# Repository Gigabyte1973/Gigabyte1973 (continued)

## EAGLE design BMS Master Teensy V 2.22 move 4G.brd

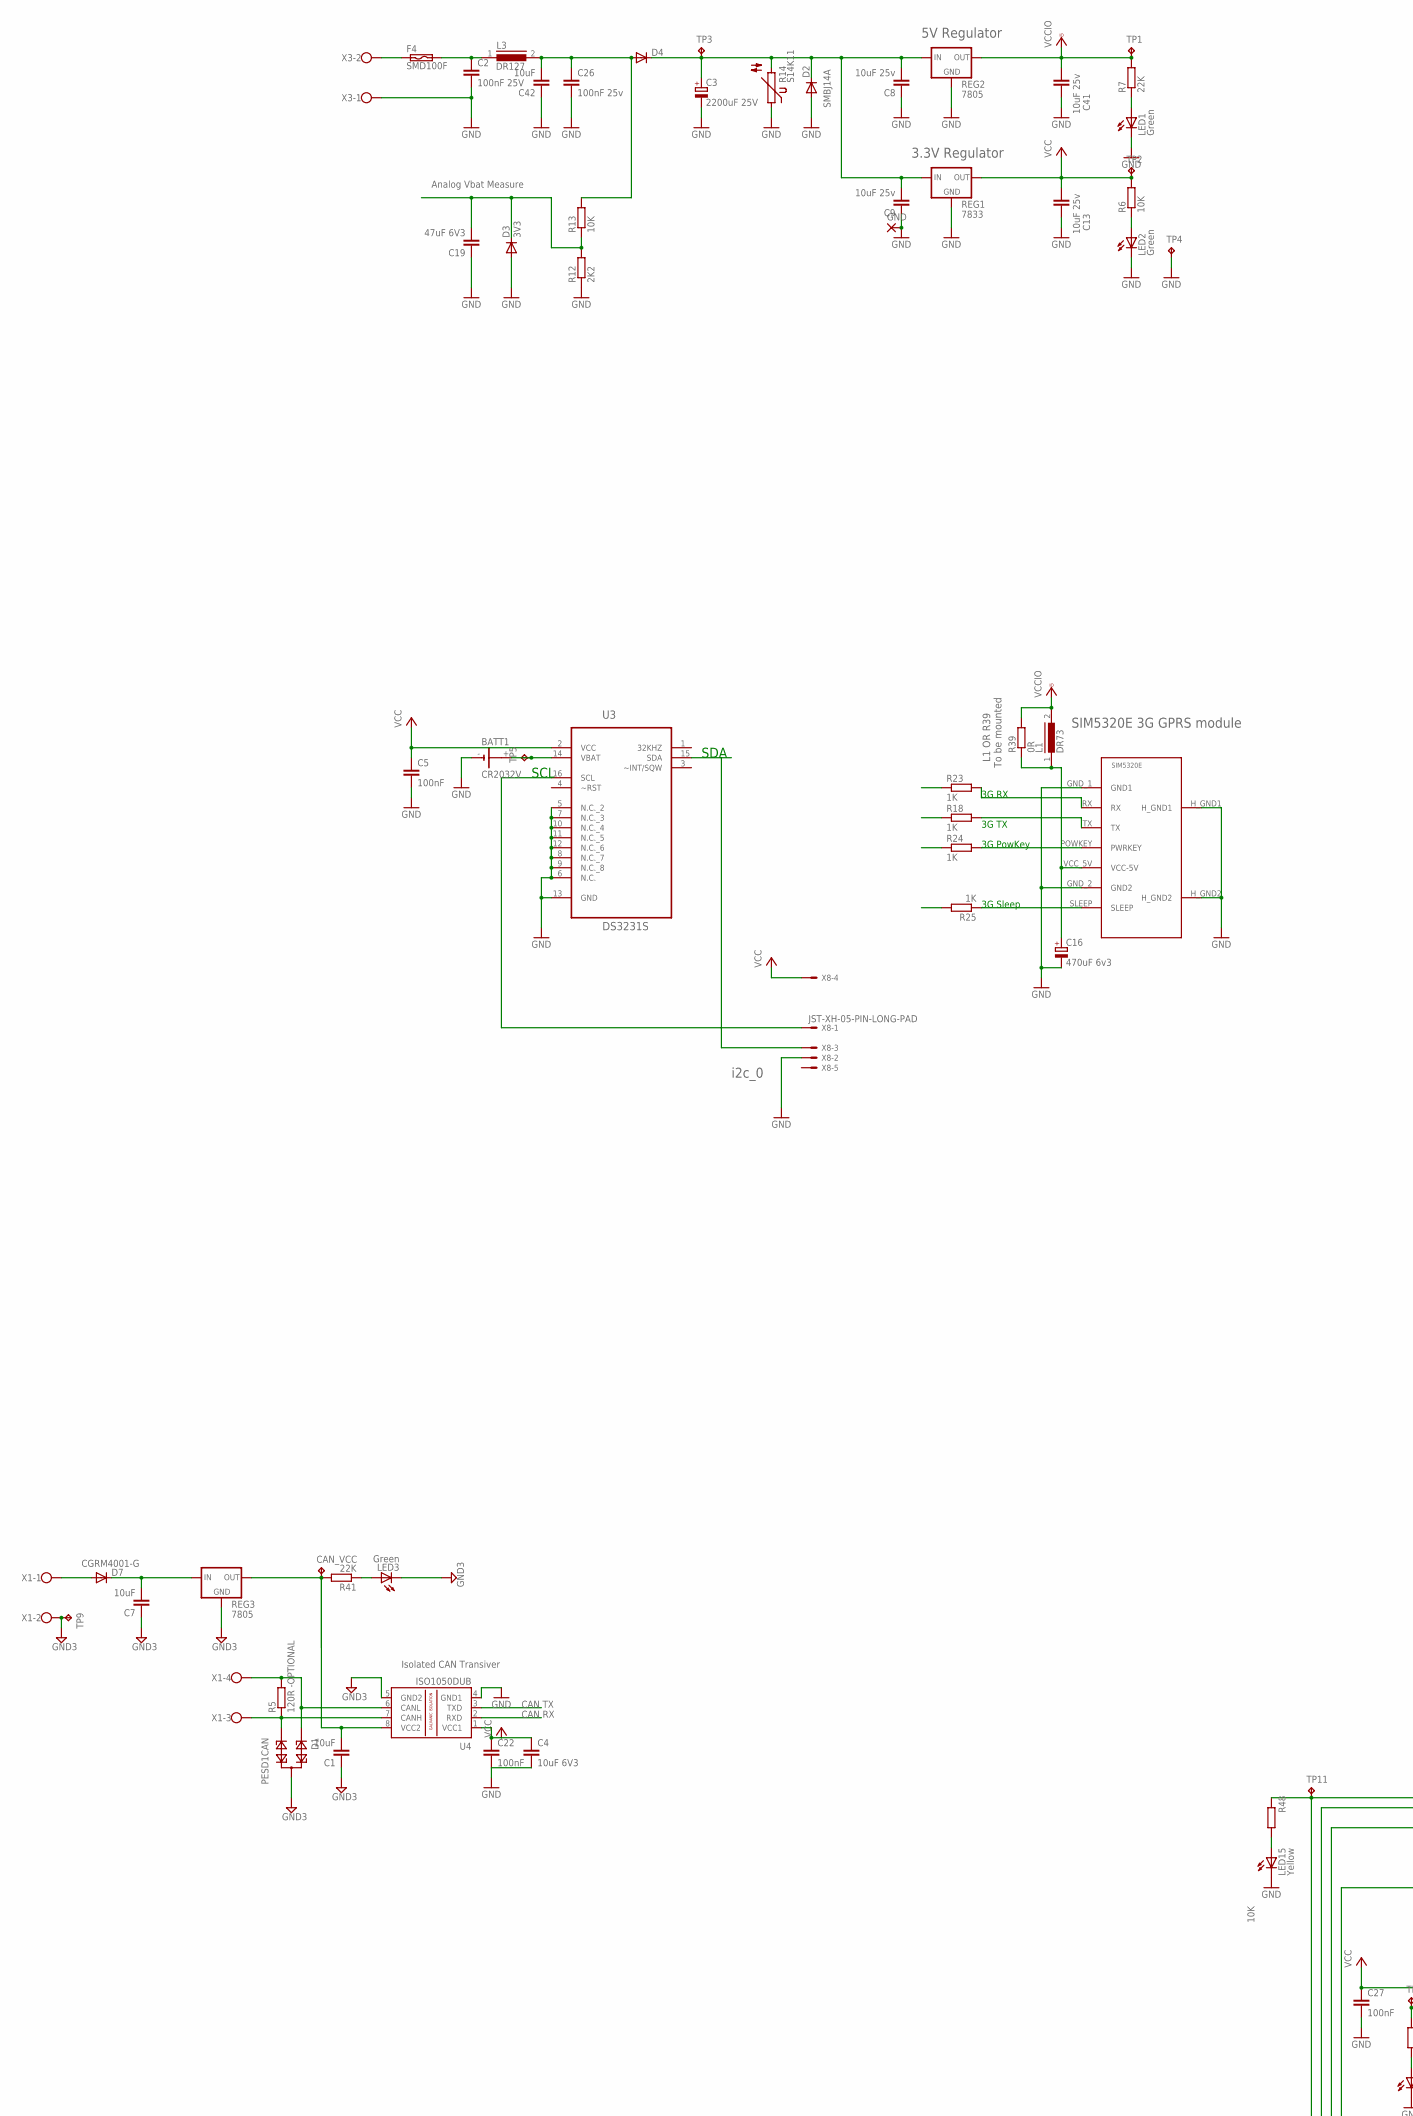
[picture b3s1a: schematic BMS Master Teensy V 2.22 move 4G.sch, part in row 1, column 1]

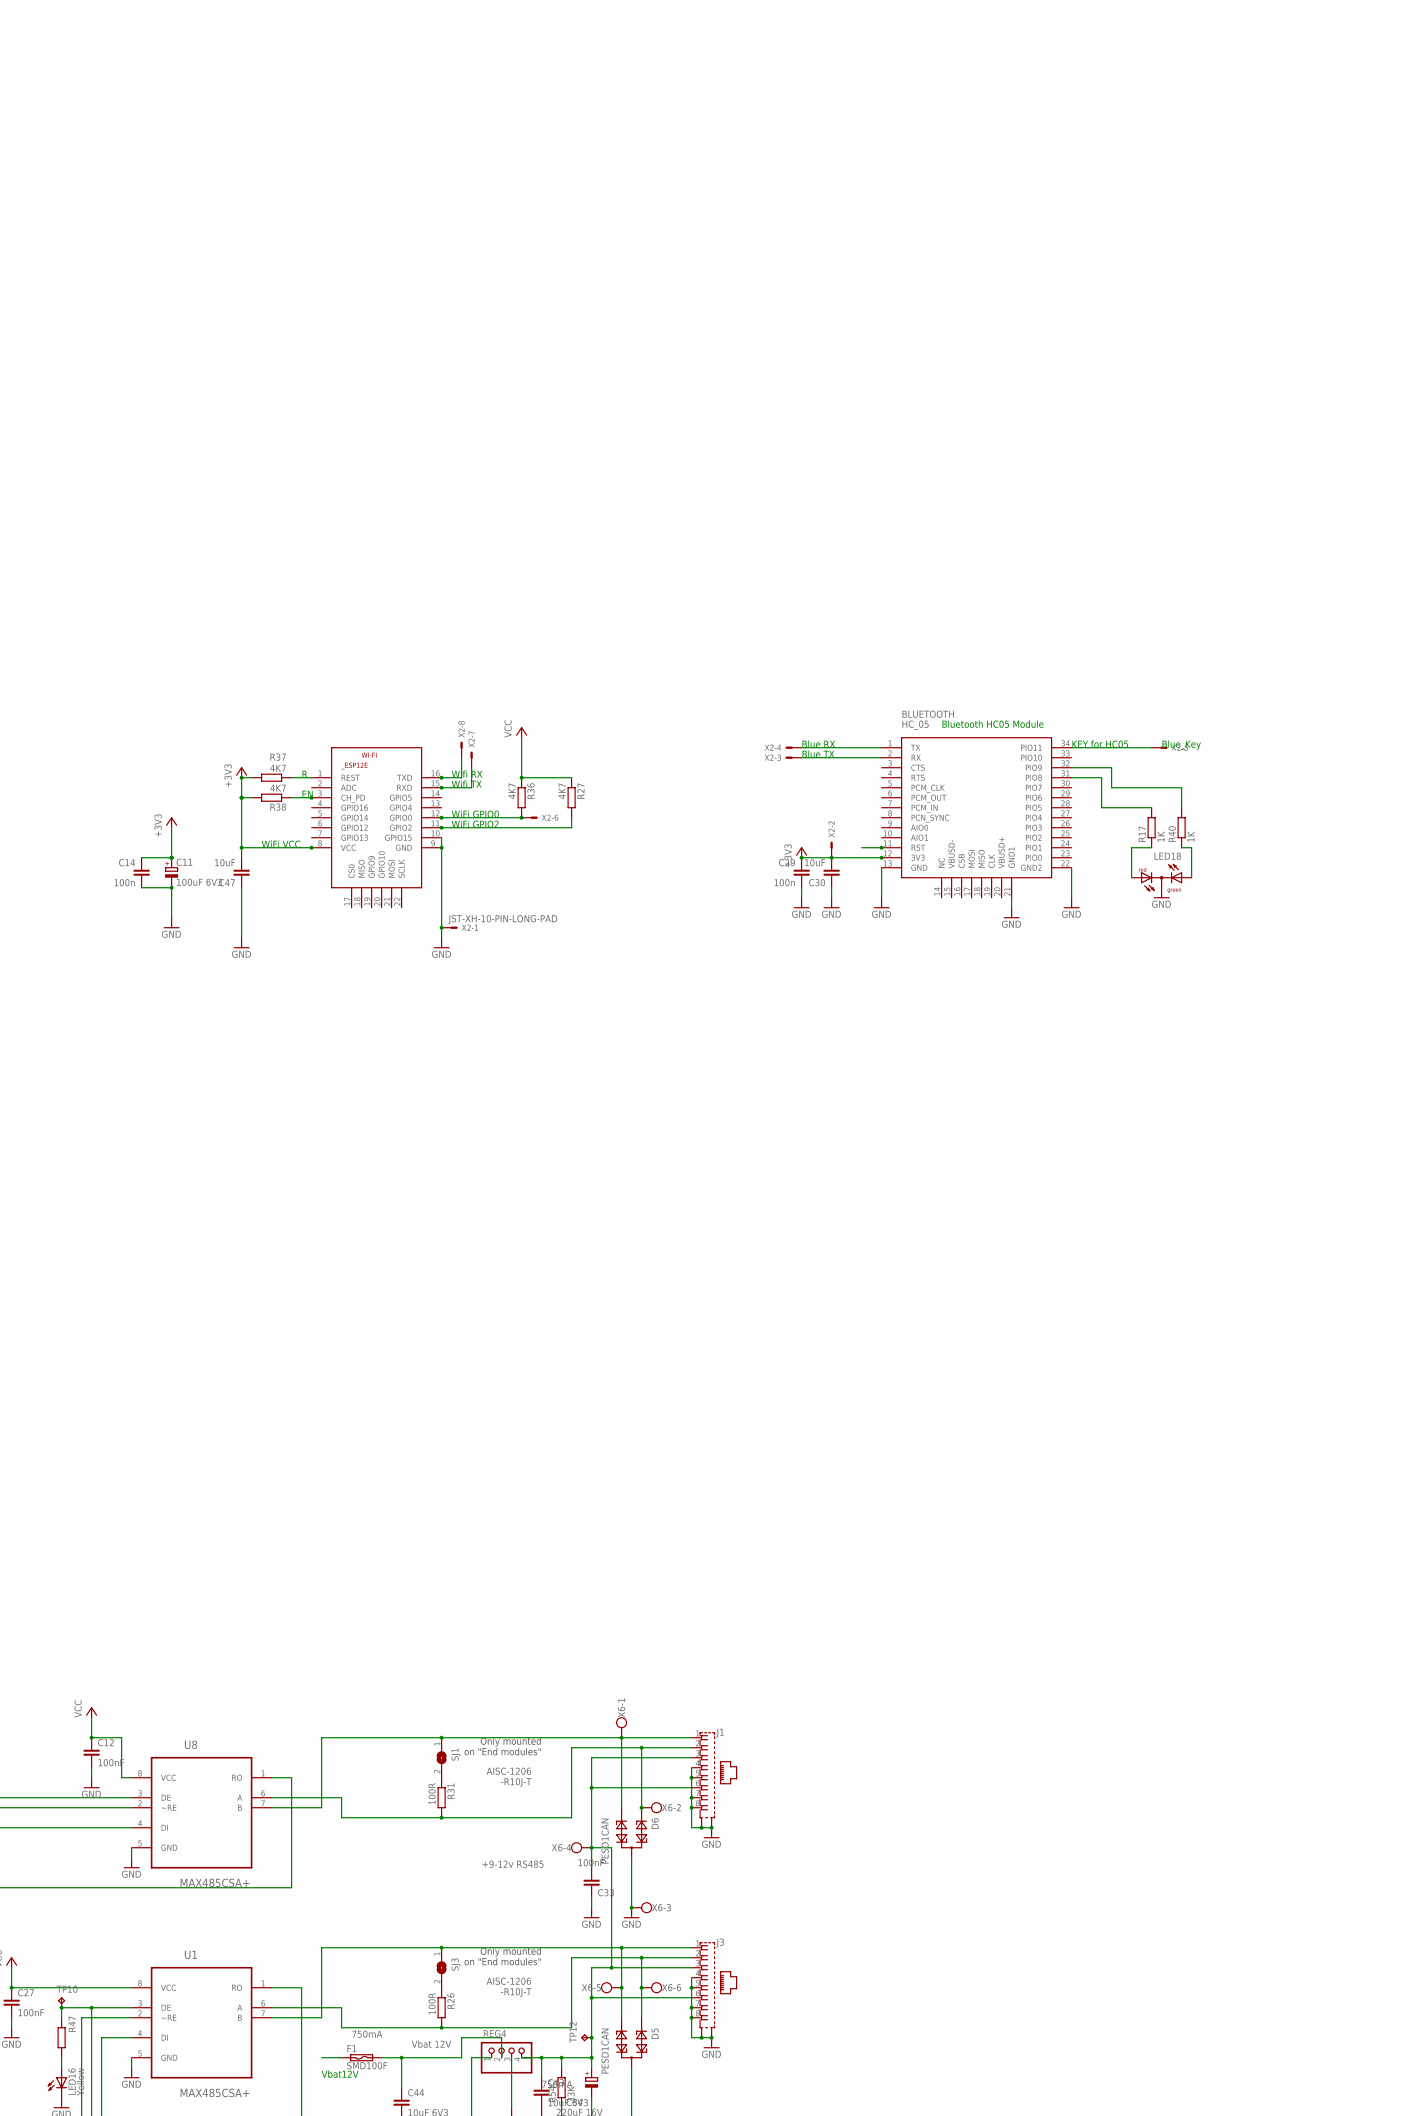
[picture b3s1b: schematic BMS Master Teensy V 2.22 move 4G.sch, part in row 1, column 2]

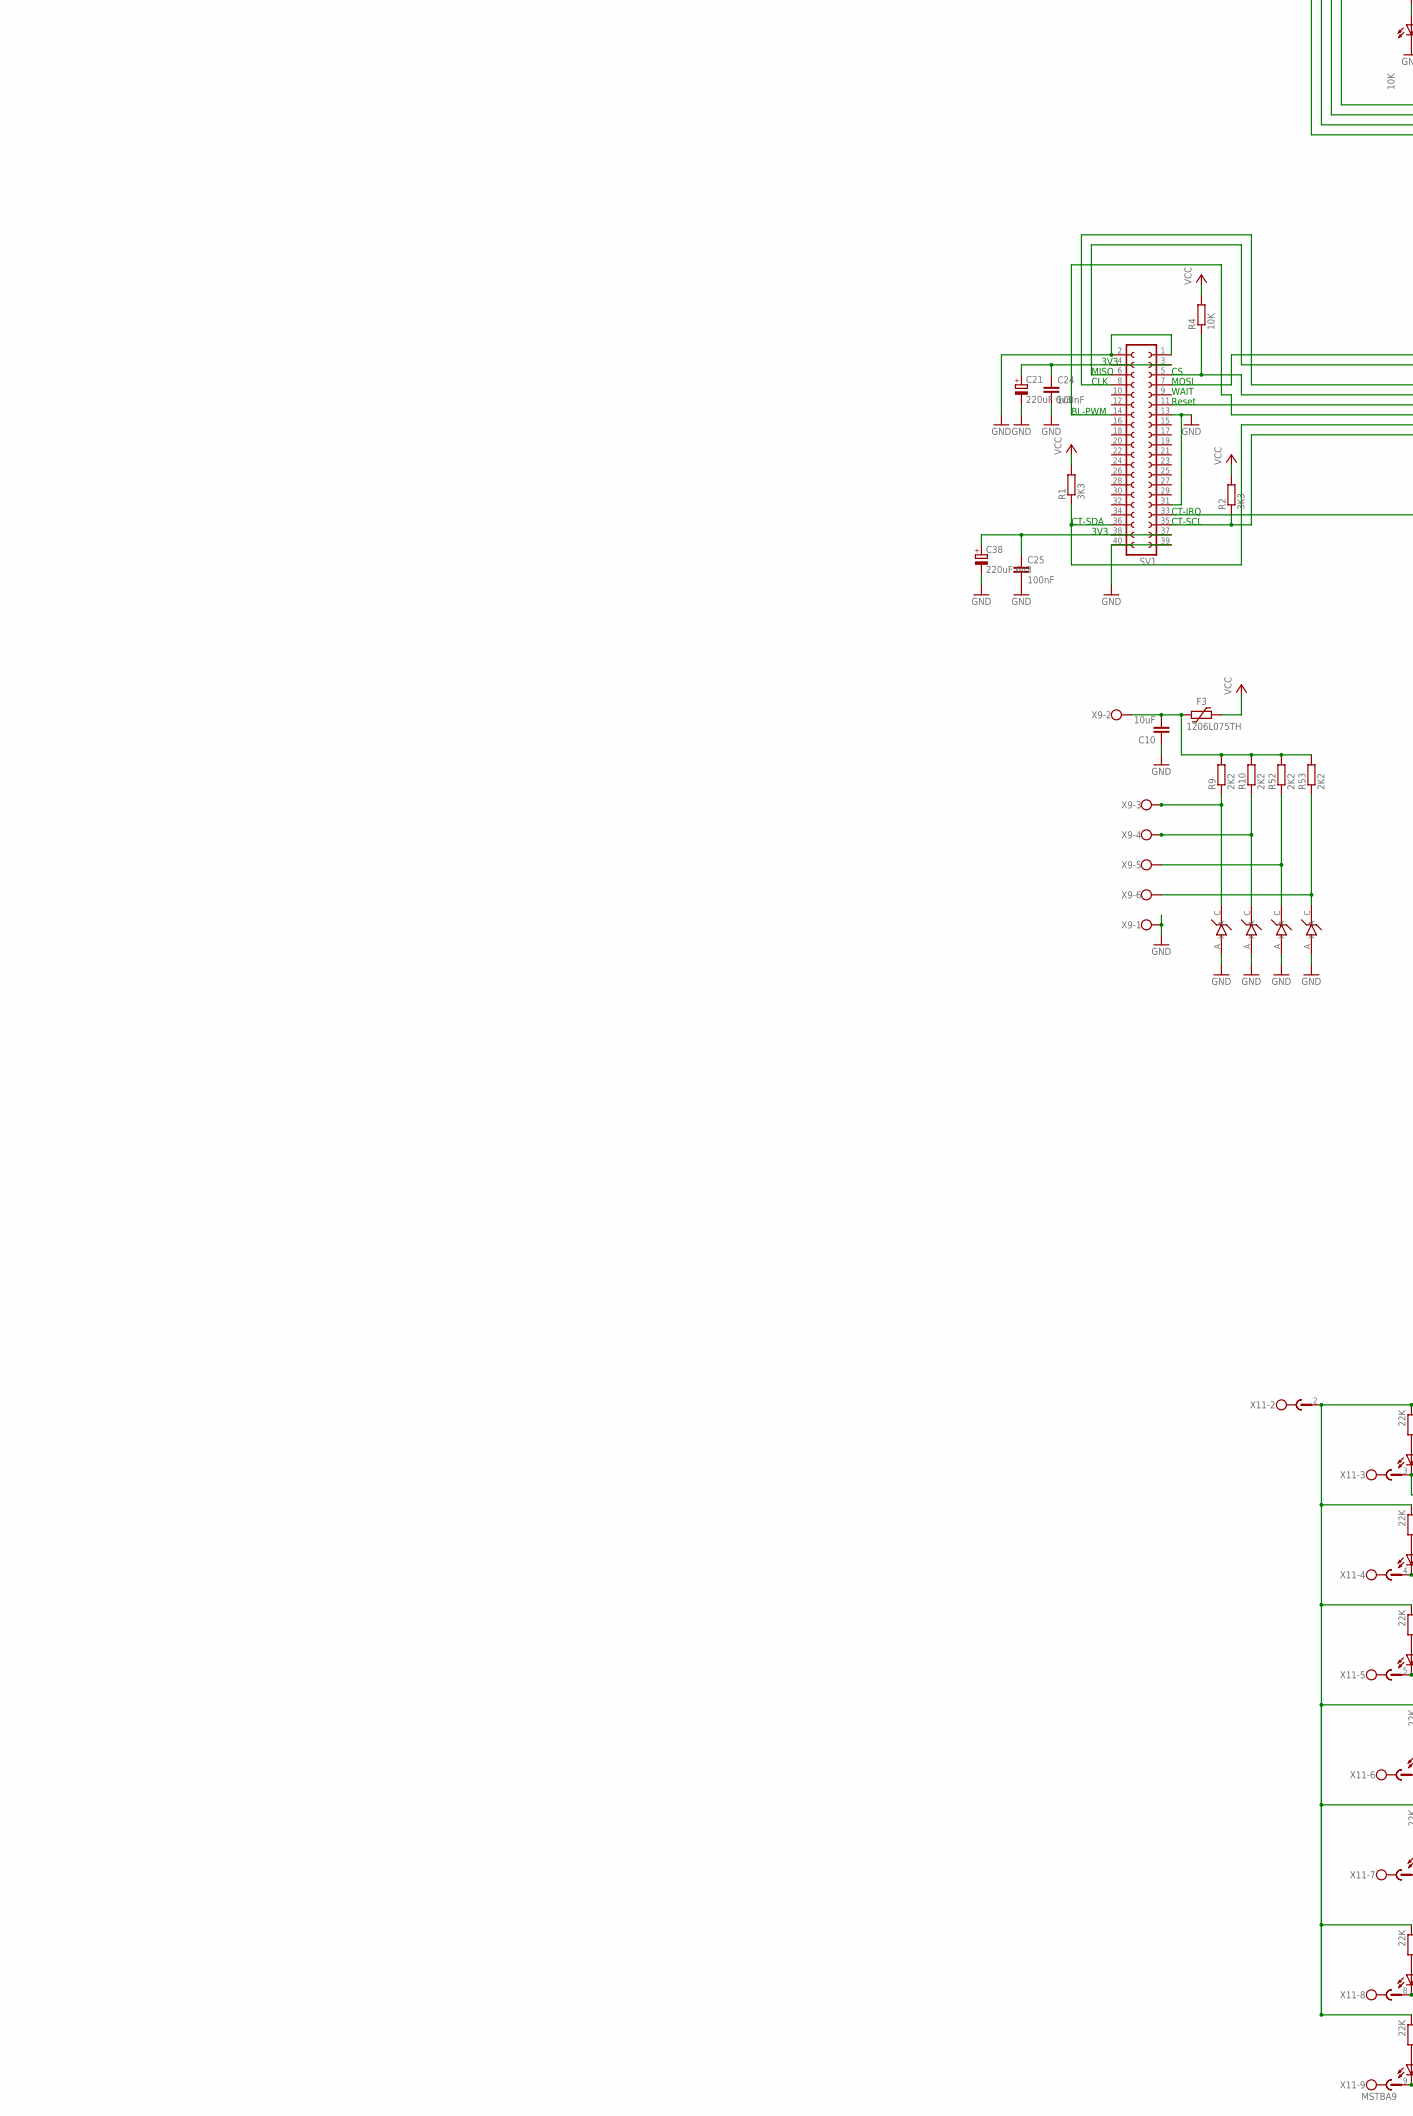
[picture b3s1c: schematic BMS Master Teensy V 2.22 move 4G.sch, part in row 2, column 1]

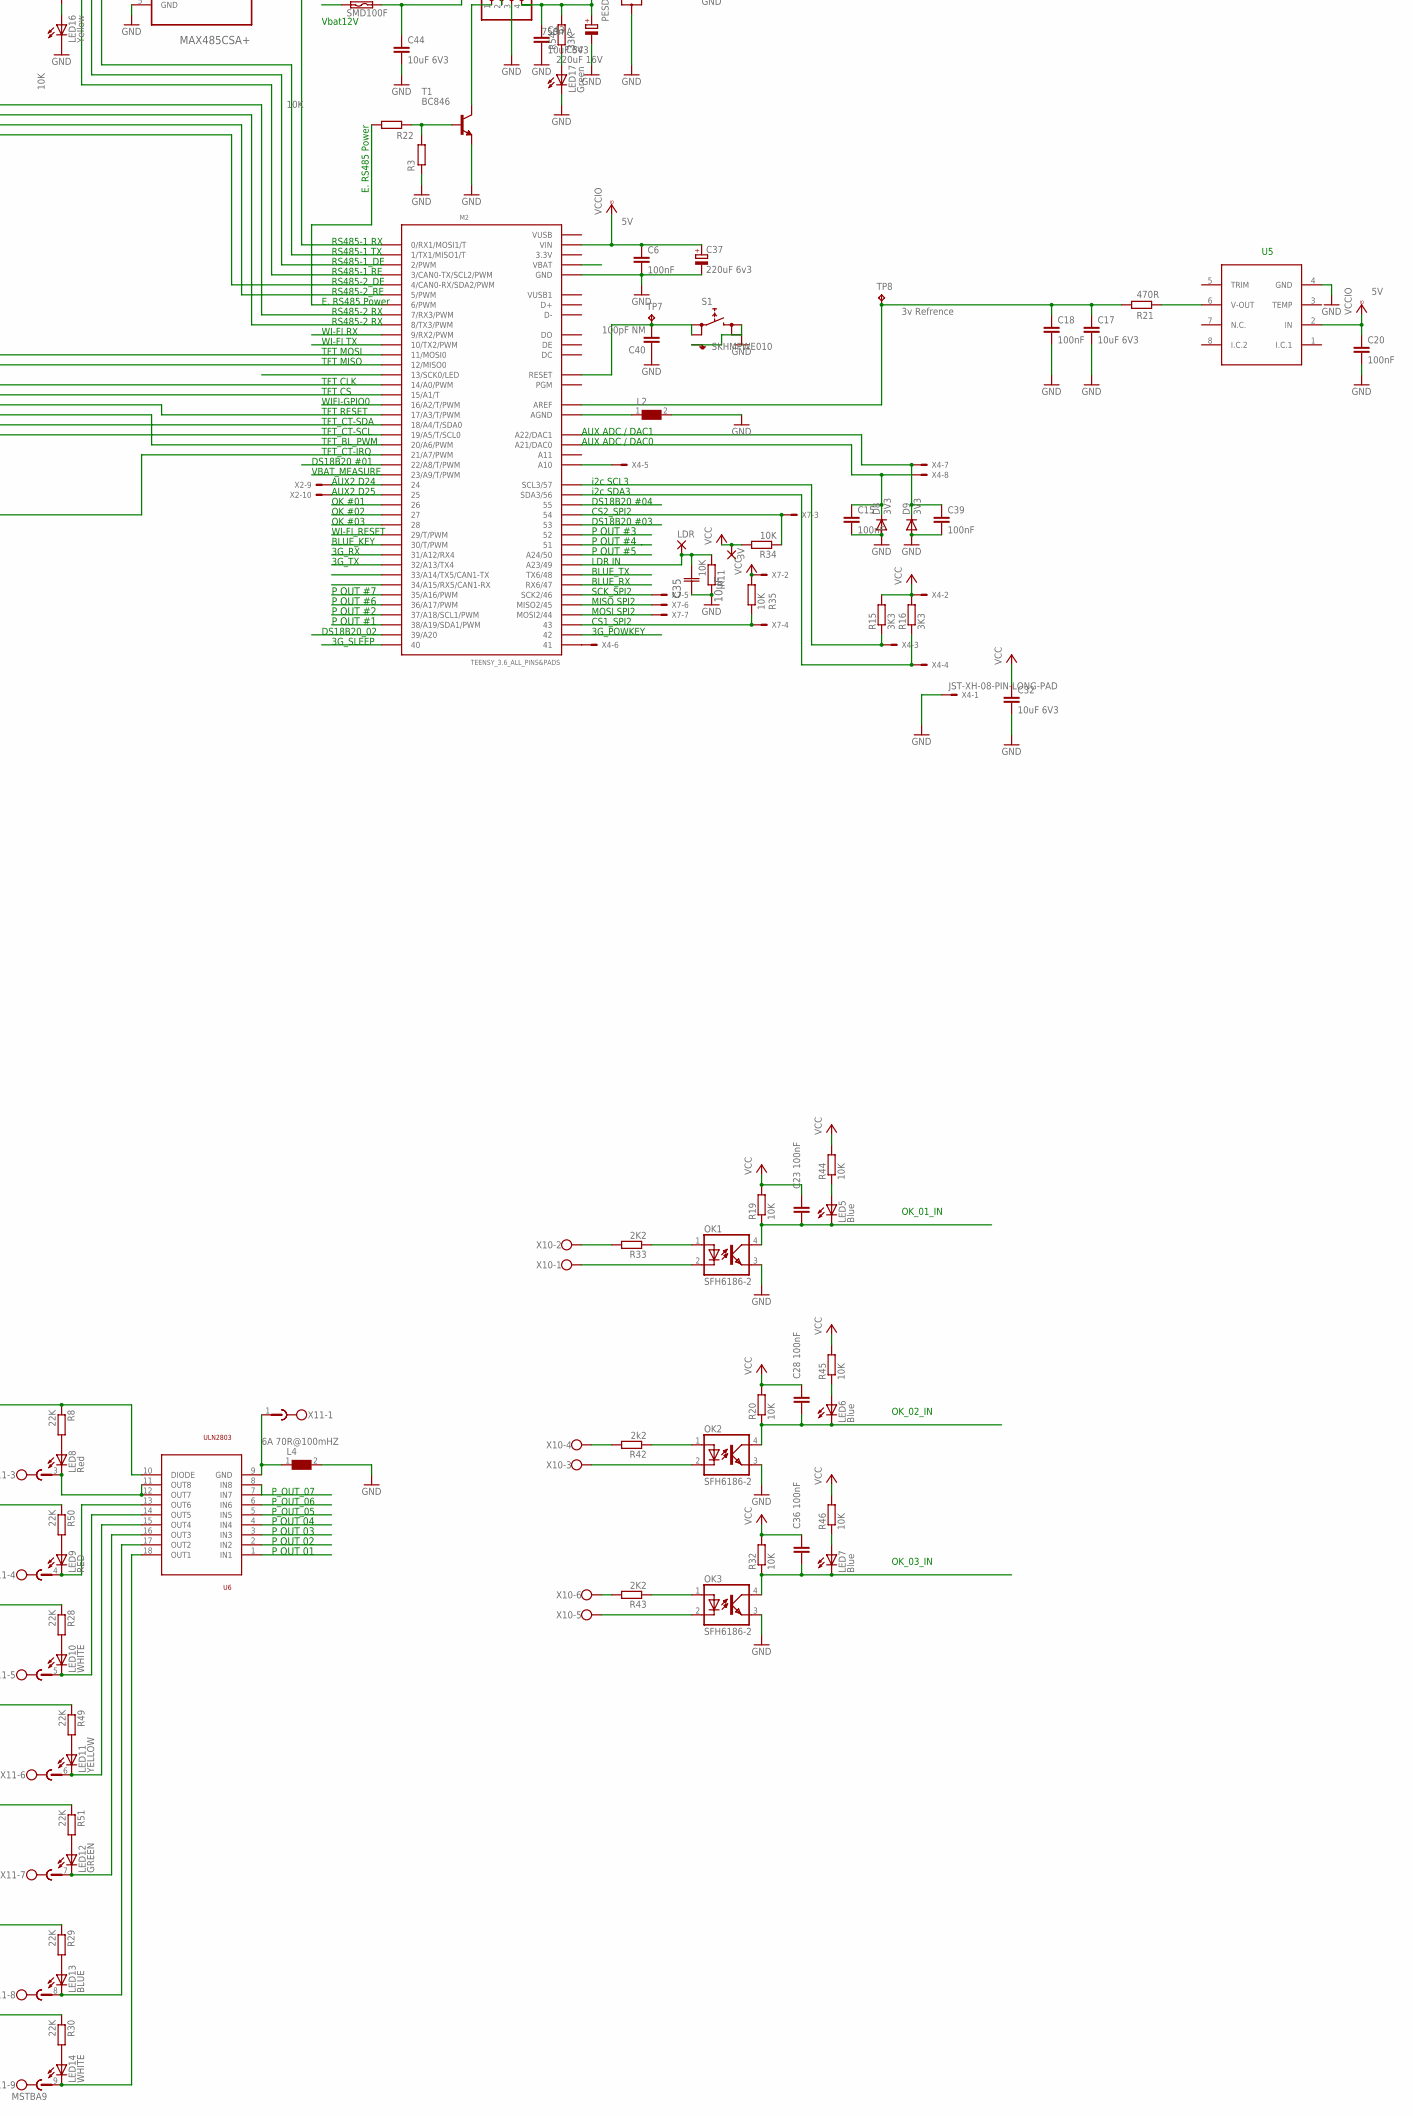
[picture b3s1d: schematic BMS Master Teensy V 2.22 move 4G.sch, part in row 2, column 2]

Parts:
3V: 1,6/0,8
BATT1: CR2032V
BLUETOOTH: HC_05; BLUETOOTH_SMD
C1, C7, C10, C30, C42, C47: 10uF; C1206
C2: 100nF 25V; C0805
C3: 2200uF 25V; E5-10,5
C4, C17, C32, C43, C44: 10uF 6V3; C1206
C5, C6, C12, C15, C18, C20, C22, C24, C25, C27, C33, C39: 100nF; C0603
C8, C9, C13, C41: 10uF 25v; C1206
C11: 100uF 6V3; CT6032
C14, C29: 100n; C0603-ROUND
C16: 470uF 6v3; CT7343
C19: 47uF 6V3; C1206
C21, C37, C38: 220uF 6v3; CT7343
C23, C28, C36: 100nF; C0805
C26: 100nF 25v; C0603
C34: 220uF 16V; CT7343
C35: 10µF; CAPC2012X140N
C40: 100pF NM; C0603
CAN_VCC: TPB2,54; B2,54
D1, D5, D6: PESD1CAN; SOT23
D2: SMBJ14A; DO214AC
D3, D8, D9: 3V3; SOD80C
D4: DIODE-SMC; SMC
D7: CGRM4001-G; SOD-123_MINI-SMA
D10, D11, D12, D13: SOD-323_ZENER_DIODE; SOD323_ST
F1, F4: SMD100F; SMD050F
F3: 1206L075TH; 1206L
GND: 1,6/0,9
J1, J3: 555153-1
L1: DR73
L2: WE-CBF-74279201_0805; 0805
L3: DR127
L4: WE-CBF-742792510_1812; 1812
LDR: 1,6/0,8
LED1, LED2, LED3, LED17: Green; CHIPLED_0805
LED5, LED6, LED7: Blue; CHIPLED_0805
LED8: Red; CHIP-LED0805
LED9: RED; CHIP-LED0805
LED10, LED14: WHITE; CHIP-LED0805
LED11: YELLOW; CHIP-LED0805
LED12: GREEN; CHIP-LED0805
LED13: BLUE; CHIP-LED0805
LED15, LED16: Yellow; CHIPLED_0805
LED18: DUOLED-RG-C; DUOLED-C-5MM
M1: SIM5320_MODULE; SIM5320E_MODULE
M2: TEENSY_3.6_ALL_PINS&PADS
OK1, OK2, OK3: SFH6186-2; SMD4-7
R1, R2, R15, R16: 3K3; R0603
R3: 1M; R0603
R4, R11, R13, R22, R34, R35, R47, R48: 10K; R0603
R5: 120R -OPTIONAL; R0603
R6, R19, R20, R32, R44, R45, R46: 10K; R0805
R7, R41: 22K; R0805
R8, R28, R29, R30, R49, R50, R51: 22K; R0603
R9, R10, R12, R52, R53: 2K2; R0603
R14: S14K11
R17, R18, R23, R24, R25, R40: 1K; R0603
R21: 470R; R0603
R26, R31: 100R; R0805
R27, R36, R37, R38: 4K7; R0603
R33, R43: 2K2; R0805
R39: 0R; R0603
R42: 2k2; R0805
R54: 33K; R0805
REG1: 7833; 78XXS
REG2, REG3: 7805; 78XXS
REG4: PINHD-1X4; 1X04
S1: SKHMPWE010; SKHMPXE010
SJ1, SJ3: SJ
SV1: FE20-2
T1: BC846; SOT23
TP1, TP2, TP3, TP4, TP5, TP7, TP8, TP9, TP12: TPB2,54; B2,54
TP10, TP11: TPB1,27; B1,27
U1, U8: MAX485CSA+; SOIC127P600X175-8N
U3: DS3231S; SOIC127P1032X265-16N
U4: ISO1050DUB; DUB-R-PDSO-G8
U5: U5; MAX6177AASA+
U6: ULN2803; SO18L
WI-FI: ESP8266-12EESP12E; ESP8266-ESP12E
X1: W237-4
X2: JST-XH-10-PIN-LONG-PAD; JST-XH-10-PACKAGE-LONG-PAD
X3: W237-102
X4: JST-XH-08-PIN-LONG-PAD; JST-XH-08-PACKAGE-LONG-PAD
X6, X9, X10: W237-6
X7: JST-XH-07-PIN-LONG-PAD; JST-XH-07-PACKAGE-LONG-PAD
X8: JST-XH-05-PIN-LONG-PAD; JST-XH-05-PACKAGE-LONG-PAD
X11: MSTBA9

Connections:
3.3V: M2.3.3V, M2.3.3V2 (3.3V), M2.3.3V3 (3.3V), M2.3.3V4 (3.3V)
3G_POWKEY: M2.42, R24.1
3G_RX: M2.31/A12 (31/A12/RX4), R18.1
3G_SLEEP: M2.40, R25.2
3G_TX: M2.32/A13 (32/A13/TX4), R23.1
18B20_VCC: C10.2, F3.2, R9.2, R10.2, R52.2, R53.2, X9.2
A10: M2.A10, X4.5
A-: D5.1, J3.2, R26.2, U1.6 (A), X6.6
A-1: D6.1, J1.2, R31.2, U8.6 (A), X6.2
AUX_ADC-DAC_1: C39.1, D9.C, M2.A22 (A22/DAC1), X4.7
B+: D5.2, J3.1, SJ3.1, U1.7 (B), X6.5
B+1: D6.2, J1.1, SJ1.1, U8.7 (B), X6.1
BL-PWM: M2.20/A6 (20/A6/PWM), SV1.14
BLUE_KEY: BLUETOOTH.34 (PIO11), M2.30 (30/T/PWM), X2.5
BLUE_RX: BLUETOOTH.1 (TX), M2.47 (RX6/47), X2.4
BLUE_TX: BLUETOOTH.2 (RX), M2.48 (TX6/48), X2.3
CAN-L: D1.1, R5.2, U4.6 (CANL), X1.4
CAN_RX: M2.34/A15 (34/A15/RX5/CAN1-RX), U4.2 (RXD)
CAN_TX: M2.33/A14 (33/A14/TX5/CAN1-TX), U4.3 (TXD)
CAN_VBAT_12V: D7.A, X1.1
CHARGE_A(1): C15.1, D8.C, M2.A21 (A21/DAC0), X4.8
CS1_SPI2: M2.43, R35.1, X7.4
CS2_SPI2: M2.54, R34.1, X7.3
CT-IRQ: M2.21/A7 (21/A7/PWM), SV1.33
D24: M2.24, X2.9
D25: M2.25, X2.10
D41: M2.41, X4.6
DCIN: C33.1, C34.+, C43.1, J1.3, J1.6, J3.3, J3.6, R54.2, REG4.4, TP12.TP, X6.4
DS18B20_01: D13.C (K), M2.22/A8 (22/A8/T/PWM), R9.1, X9.3
DS18B20_02: D12.C (K), M2.39/A20, R10.1, X9.4
DS18B20_03: D11.C (K), M2.53, R52.1, X9.5
DS18B20_04: D10.C (K), M2.55, R53.1, X9.6
E_RS485_POWER: M2.6 (6/PWM), R22.1
GND: BATT1.-, BLUETOOTH.13 (GND), BLUETOOTH.21 (GND1), BLUETOOTH.22 (GND2), C2.2, C3.-, C4.2, C5.2, C6.2, C8.1, C9.1, C10.1, C11.-, C12.2, C13.1, C14.2, C15.2, C16.-, C17.2, C18.2, C19.1, C20.2, C21.-, C22.2, C24.2, C25.2, C26.2, C27.2, C29.2, C30.1, C32.2, C33.2, C34.-, C35.1 (C1), C37.-, C38.-, C39.2, C40.1, C41.1, C42.1, C43.2, C44.2, C47.1, D2.A, D3.A, D5.3, D6.3, D8.A, D9.A, D10.A, D11.A, D12.A, D13.A, GND.1, J1.4, J1.5, J1.7, J1.8, J1.G1 (S1), J1.G2 (S2), J3.4, J3.5, J3.7, J3.8, J3.G1 (S1), J3.G2 (S2), L2.2, L4.2, LED1.C, LED2.C, LED15.C, LED16.C, LED17.C, LED18.C, M1.GND_1 (GND1), M1.GND_2 (GND2), M1.H_GND1, M1.H_GND2, M2.GND, M2.GND1 (GND), M2.GND2 (GND), M2.GND3 (GND), M2.GND4 (GND), M2.GND5 (GND), M2.GND6 (GND), OK1.3 (EMIT), OK2.3 (EMIT), OK3.3 (EMIT), R3.2, R11.2, R12.1, R14.1, REG1.GND, REG2.GND, REG4.3, S1.3 (2.1), S1.4 (2.2), S1.5 (SH), SV1.1, SV1.2, SV1.13, SV1.31, SV1.39, SV1.40, T1.2 (E), TP4.TP, U1.5 (GND), U3.5 (N.C._2), U3.6 (N.C.), U3.7 (N.C._3), U3.8 (N.C._7), U3.9 (N.C._8), U3.10 (N.C._4), U3.11 (N.C._5), U3.12 (N.C._6), U3.13 (GND), U4.4 (GND1), U5.4 (GND), U8.5 (GND), WI-FI.9 (GND), WI-FI.10 (GPIO15), X2.1, X3.1, X4.1, X6.3, X8.2, X9.1
GND3-CAN: C1.1, C7.1, D1.3, LED3.C, REG3.GND, TP9.TP, U4.5 (GND2), X1.2
GND-FILTERED: L4.1, U6.9 (GND), X11.1
LDR_A23: C35.2 (C2), LDR.1, M2.49 (A23/49), R11.1
MISO_SPI2: M2.45 (MISO2/45), X7.6
MOSI_SPI2: M2.44 (MOSI2/44), X7.7
unnamed: M2.0 (0/RX1/MOSI1/T), U1.1 (RO)
unnamed: M2.1 (1/TX1/MISO1/T), U1.4 (DI)
unnamed: L2.1, M2.AGND
unnamed: LED17.A, R54.1
unnamed: C2.1, F4.2, L3.1
unnamed: LED16.A, R47.1
unnamed: R3.1, R22.2, T1.1 (B)
unnamed: LED15.A, R48.1
unnamed: F4.1, X3.2
unnamed: LED11.A, R49.2
unnamed: BATT1.+, TP5.TP, U3.14 (VBAT)
unnamed: M1.TX, R18.2
unnamed: LED18.AR, R17.1
unnamed: LED3.A, R41.1
unnamed: LED9.A, R50.2
unnamed: M1.RX, R23.2
unnamed: D1.2, R5.1, U4.7 (CANH), X1.3
unnamed: LED18.AX (AG), R40.1
unnamed: LED12.A, R51.2
unnamed: LED2.A, R6.1
unnamed: LED1.A, R7.1
unnamed: C44.1, F1.2, REG4.2
unnamed: LED8.A, R8.2
unnamed: OK1.1 (A), R33.1
unnamed: R33.2, X10.2
unnamed: OK3.1 (A), R43.1
unnamed: R43.2, X10.6
unnamed: R42.2, X10.4
unnamed: BLUETOOTH.32 (PIO9), R40.2
unnamed: BLUETOOTH.31 (PIO8), R17.2
unnamed: R26.1, SJ3.2
unnamed: R21.2, U5.6 (V-OUT)
unnamed: M1.POWKEY (PWRKEY), R24.2
unnamed: M1.SLEEP, R25.1
unnamed: OK2.2 (C), X10.3
unnamed: OK3.2 (C), X10.5
unnamed: C7.2, D7.C, REG3.IN
unnamed: LED10.A, R28.2
unnamed: LED13.A, R29.2
unnamed: LED14.A, R30.2
unnamed: OK1.2 (C), X10.1
unnamed: OK2.1 (A), R42.1
unnamed: LED5.A, R44.1
unnamed: LED6.A, R45.1
unnamed: R31.1, SJ1.2
unnamed: LED7.A, R46.1
OK_01_IN: C23.2, LED5.C, M2.26, OK1.4 (COL), R19.1
OK_02_IN: C28.2, LED6.C, M2.27, OK2.4 (COL), R20.1
OK_03_IN: C36.2, LED7.C, M2.28, OK3.4 (COL), R32.1
OUT_01: LED14.C, U6.18 (OUT1), X11.9
OUT_02: LED13.C, U6.17 (OUT2), X11.8
OUT_03: LED12.C, U6.16 (OUT3), X11.7
OUT_04: LED11.C, U6.15 (OUT4), X11.6
OUT_05: LED10.C, U6.14 (OUT5), X11.5
OUT_06: LED9.C, U6.13 (OUT6), X11.4
OUT_07: LED8.C, U6.11 (OUT8), U6.12 (OUT7), X11.3
OUT_VCC_VOLTAGE: R8.1, R28.1, R29.1, R30.1, R49.1, R50.1, R51.1, U6.10 (DIODE), X11.2
P_OUT_01: M2.38/A19 (38/A19/SDA1/PWM), U6.1 (IN1)
P_OUT_02: M2.37/A18 (37/A18/SCL1/PWM), U6.2 (IN2)
P_OUT_03: M2.52, U6.3 (IN3)
P_OUT_04: M2.51, U6.4 (IN4)
P_OUT_05: M2.50 (A24/50), U6.5 (IN5)
P_OUT_06: M2.36/A17 (36/A17/PWM), U6.6 (IN6)
P_OUT_07: M2.35/A16 (35/A16/PWM), U6.7 (IN7), U6.8 (IN8)
RESET: C40.2, M2.RESET, S1.1 (1.1), S1.2 (1.2), TP7.TP
RS485-1_DE: M2.2 (2/PWM), R47.2, TP10.TP, U1.3 (DE)
RS485-1_RE: M2.3 (3/CAN0-TX/SCL2/PWM), U1.2 (~RE)
RS485-2_DE: M2.4 (4/CAN0-RX/SDA2/PWM), R48.2, TP11.TP, U8.3 (DE)
RS485-2_RE: M2.5 (5/PWM), U8.2 (~RE)
RS485-2_RX: M2.7 (7/RX3/PWM), U8.1 (RO)
RS485-2_TX: M2.8 (8/TX3/PWM), U8.4 (DI)
RS485_POWER: REG4.1, T1.3 (C)
SCK_SPI2: M2.46 (SCK2/46), X7.5
SCL: M2.19/A5 (19/A5/T/SCL0), R2.1, SV1.35, U3.16 (SCL), X8.1
SCL3: M2.57 (SCL3/57), R15.1, X4.3
SDA: M2.18/A4 (18/A4/T/SDA0), R1.1, SV1.36, U3.15 (SDA), X8.3
SDA3: M2.56 (SDA3/56), R16.1, X4.4
SIM5320E_VCC: C16.+, L1.1, M1.VCC_5V (VCC-5V), R39.1
TFT-SCK: M2.14/A0 (14/A0/PWM), SV1.8
TFT_CS: M2.15/A1 (15/A1/T), R4.1, SV1.5
TFT_MISO: M2.12 (12/MISO0), SV1.6
TFT_MOSI: M2.11 (11/MOSI0), SV1.7
TFT_RESET: M2.17/A3 (17/A3/T/PWM), SV1.11
VBAT12V: C3.+, C8.2, C9.2, D2.C, D4.C, F1.1, R14.2, REG1.IN, REG2.IN, TP3.TP
VBAT_12V: C26.1, C42.2, D4.A, L3.2, R13.2
VBAT_MEASURE: C19.2, D3.C, M2.23/A9 (23/A9/T/PWM), R12.2, R13.1
VCC3V1: C1.2, CAN_VCC.TP, R41.2, REG3.OUT, U4.8 (VCC2)
VCC3V3: 3V.1, BLUETOOTH.12 (3V3), C4.1, C5.1, C11.+, C12.1, C13.2, C14.1, C21.+, C22.1, C23.1, C24.1, C25.1, C27.1, C28.1, C29.1, C30.2, C32.1, C36.1, C38.+, C47.2, F3.1, R1.2, R2.2, R4.2, R6.2, R15.2, R16.2, R19.2, R20.2, R27.1, R32.2, R34.2, R35.2, R36.1, R37.2, R38.2, R44.2, R45.2, R46.2, REG1.OUT, SV1.3, SV1.4, SV1.37, SV1.38, TP2.TP, U1.8 (VCC), U3.2 (VCC), U4.1 (VCC1), U8.8 (VCC), WI-FI.8 (VCC), X2.2, X4.2, X7.2, X8.4
VCC5V: C6.1, C20.1, C37.+, C41.2, L1.2, M2.VIN, R7.2, R39.2, REG2.OUT, TP1.TP, U5.2 (IN)
VREF_3V: C17.1, C18.1, M2.AREF, R21.1, TP8.TP
VUSB: M2.VUSB
VUSB1: M2.VUSB1
WI-FI_RESET: M2.29 (29/T/PWM), R37.1, WI-FI.1 (REST)
WI-FI_RX: M2.9 (9/RX2/PWM), WI-FI.16 (TXD), X2.8
WI-FI_TX: M2.10 (10/TX2/PWM), WI-FI.15 (RXD), X2.7
WIFI-CH_PD: R38.1, WI-FI.3 (CH_PD)
WIFI-GPIO0: M2.16/A2 (16/A2/T/PWM), R36.2, WI-FI.12 (GPIO0), X2.6
WIFI-GPIO2: R27.2, WI-FI.11 (GPIO2)

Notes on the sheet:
3.3V Regulator
5V Regulator
Isolated CAN Transiver
CT-IRQ
CT-SCL
CT-SDA
MISO
MOSI
CLK
WAIT
Reset
BL-PWM
3V3
SCL
SDA
3v Refrence
KEY for HC05
Bluetooth HC05 Module
Blue TX
Blue RX
Blue_Key
BLUE_KEY
BLUE_RX
BLUE_TX
AUX ADC / DAC0
AUX ADC / DAC1
WI-FI TX
WI-FI RX
Only mounted on "End modules"
AISC-1206 -R10J-T
E. RS485 Power
MOSI SPI2
MISO SPI2
SCK_SPI2
750mA
Wifi TX
Wifi RX
WiFi GPIO0
WiFi GPIO2
WiFi VCC

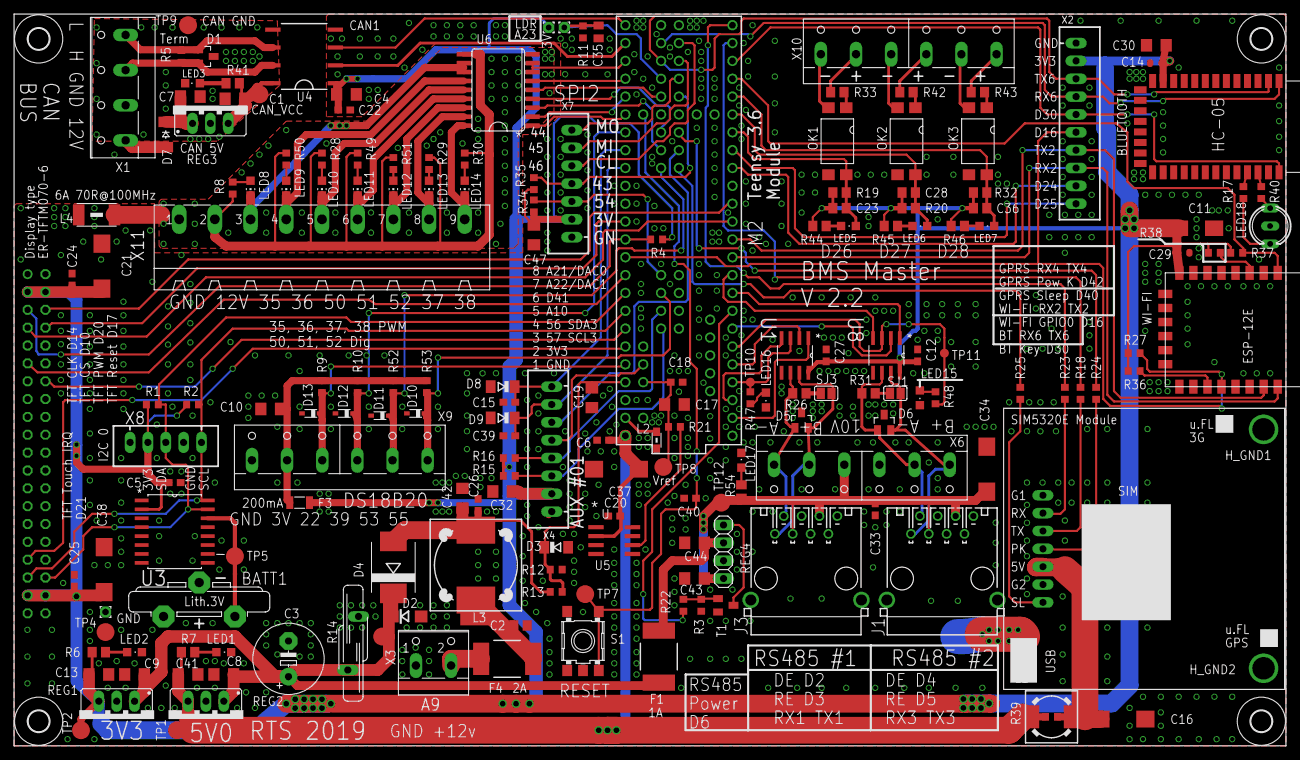
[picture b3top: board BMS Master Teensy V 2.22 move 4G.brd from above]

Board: 2 copper layers, 181.0 x 104.1 mm, 189 parts (1 on the bottom side), 135 nets.

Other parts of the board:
U$2, U$4, U$6, U$7: 3,0

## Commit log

2019-11-26 Add files via upload
    BMS V2.22, moved 4G modem
2019-11-26 Add files via upload
    BMS Current sensor board. V1.11
2019-11-26 Add files via upload
    BMS Battery SLAVE module V3.33
2019-11-26 Add files via upload
    Current SLAVE V1.0
2019-11-26 Add files via upload
    BMS Jesper 4G V1.0
2019-11-26 Add files via upload
    Tiny GSM (orig) & RA8876 (modded) Libs
2019-12-02 BMS Master V2.3
    Store local charge time finished to EE-rom.
    Push Summer time from Blynk
    Make Outdoor TXT in display change color according to temp.
    Move hardcoded constants to ini file
    Routine to enable DC-DC when 12v get below threshold (ini file)
    Display (Fuel cap open) if Opto in D26 is High
